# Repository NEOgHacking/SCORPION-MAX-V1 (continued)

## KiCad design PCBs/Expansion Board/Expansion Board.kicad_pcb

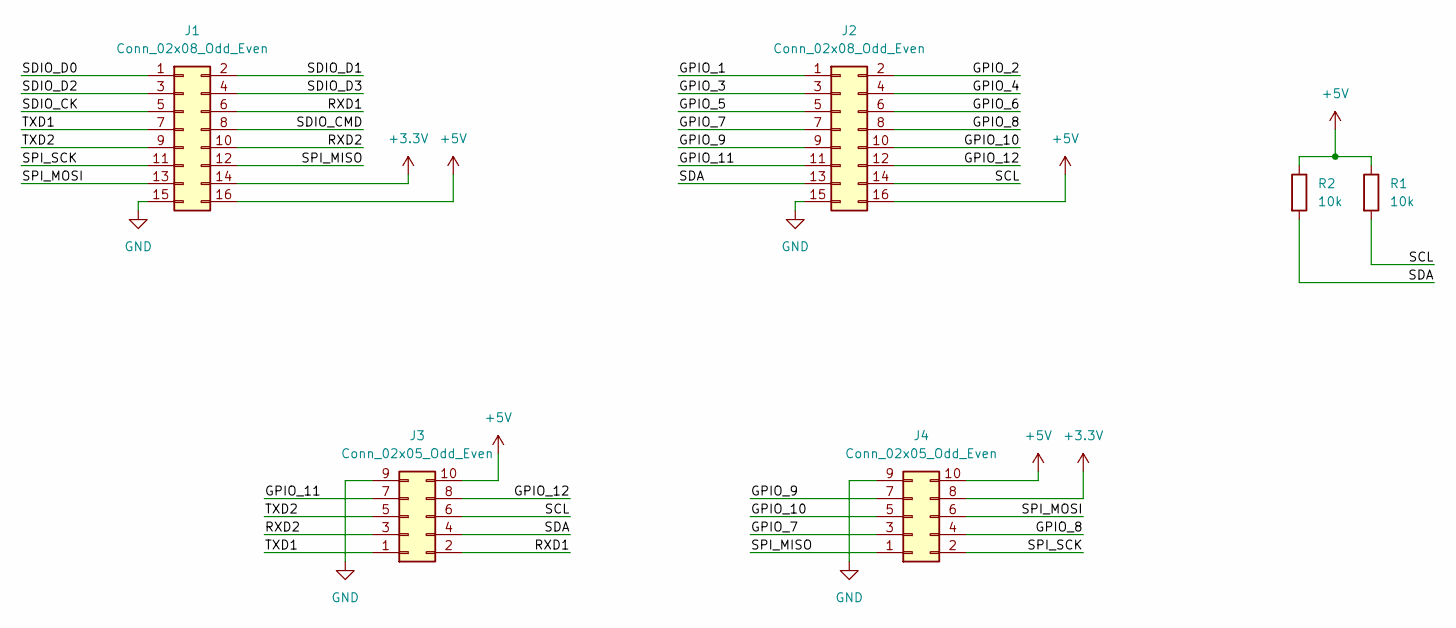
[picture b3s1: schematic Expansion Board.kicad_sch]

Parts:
J1, J2: Conn_02x08_Odd_Even; PinHeader_2x08_P2.54mm_Vertical
J3, J4: Conn_02x05_Odd_Even; IDC-Header_2x05_P2.54mm_Vertical
R1, R2: 10k; R_0603_1608Metric

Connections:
+3.3V: J1.14, J4.8
+5V: J1.16, J2.16, J3.10, J4.10, R1.1, R2.1
/GPIO_1: J2.1
/GPIO_2: J2.2
/GPIO_3: J2.3
/GPIO_4: J2.4
/GPIO_5: J2.5
/GPIO_6: J2.6
/GPIO_7: J2.7, J4.3
/GPIO_8: J2.8, J4.4
/GPIO_9: J2.9, J4.7
/GPIO_10: J2.10, J4.5
/GPIO_11: J2.11, J3.7
/GPIO_12: J2.12, J3.8
/RXD1: J1.6, J3.2
/RXD2: J1.10, J3.3
/SCL: J2.14, J3.6, R1.2
/SDA: J2.13, J3.4, R2.2
/SDIO_CK: J1.5
/SDIO_CMD: J1.8
/SDIO_D0: J1.1
/SDIO_D1: J1.2
/SDIO_D2: J1.3
/SDIO_D3: J1.4
/SPI_MISO: J1.12, J4.1
/SPI_MOSI: J1.13, J4.6
/SPI_SCK: J1.11, J4.2
/TXD1: J1.7, J3.1
/TXD2: J1.9, J3.5
GND: J1.15, J2.15, J3.9, J4.9

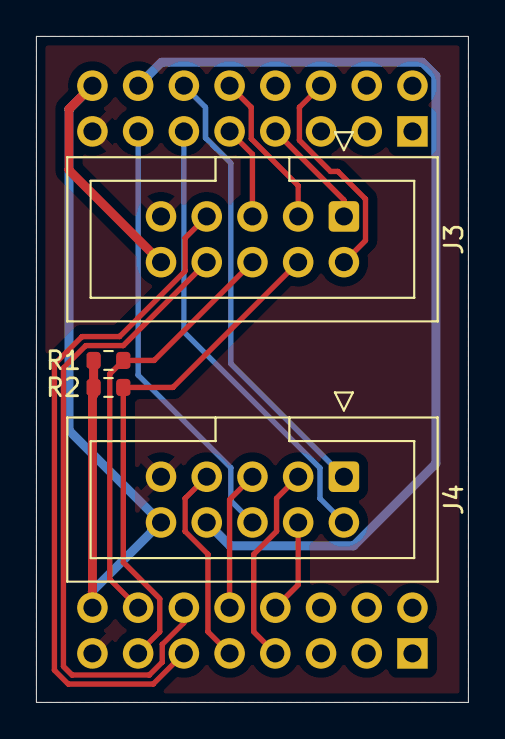
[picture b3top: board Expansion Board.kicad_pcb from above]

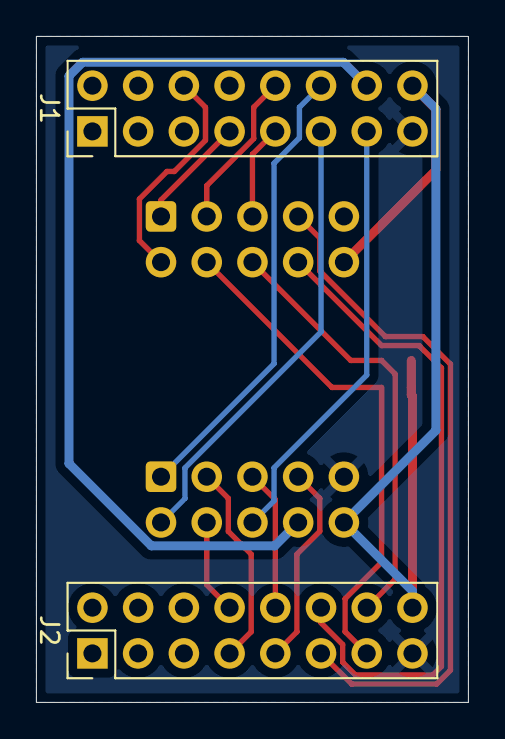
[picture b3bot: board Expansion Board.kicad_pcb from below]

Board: 2 copper layers, 24.0 x 37.0 mm, 6 parts (2 on the bottom side), 18 nets.

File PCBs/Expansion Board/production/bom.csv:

Designator,Footprint,Quantity,Value,LCSC Part #
"J1, J2",PinHeader_2x08_P2.54mm_Vertical,2,Conn_02x08_Odd_Even,
"J3, J4",IDC-Header_2x05_P2.54mm_Vertical,2,Conn_02x05_Odd_Even,
"R1, R2",0603,2,10k,

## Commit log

2026-01-10 git is so hard to use
2026-01-11 Updated KiCad files and made 3D files for expansion board and thermister board
2026-01-11 Updated all the files so its up to date
2026-01-11 Added Firmware for Marlin
2026-01-11 Modify header level in README.md
    Changed header from H1 to H3 for better hierarchy.
2026-01-11 Replace logo image in README
    Updated logo image in README.md to a new source URL.
2026-01-11 Update README with project details and images
    Added an image and expanded project description for clarity.
2026-01-11 Fix README formatting and enhance description
    Corrected formatting and improved readability of the README.
2026-01-11 Expand README with project reasoning and specs
    Added detailed specifications and reasoning for the mainboard design.
2026-01-11 Fix formatting and add newline in README.md
    Corrected formatting and added newline at end of file.
2026-01-11 Add USB port details to README
2026-01-11 Update README with schematic, PCB, and BOM information
    Added sections for schematic, PCB, and BOM details.
2026-01-11 Add images for PCB and related boards in README
2026-01-11 Add credits section to README
    Added credits section to acknowledge contributors.
2026-01-11 Added schematics in pdf format for the boards and interactive BOMs
2026-01-11 Updated render
2026-01-11 updated .blend
2026-01-11 Added pictures of prices in the BOM
2026-01-11 Fix typos and grammar in README.md
    Corrected typos and improved grammar in the README.
2026-01-11 Enhance README with firmware details and clarifications
    Added firmware information and updated component descriptions.
2026-01-11 Revise README for mainboard features and specifications
    Updated the README to improve clarity and detail about the main board's capabilities, including its specifications and intended use.
2026-01-11 Revise README section titles and add design overview
    Updated section titles and added a description of the board's design features.
2026-01-11 Enhance design description in README
    Expanded the design section to include details about PCB trace width and layout.
2026-01-11 Fix JLCPCB order price statement in README
    Corrected the pricing statement for the JLCPCB order.
2026-01-12 Made final changes before submiting
2026-01-12 Added start of video render
2026-01-14 Added .csv BOMs
    added .csv files
2026-01-14 Include schematic images in README
    Added images of schematics for various boards to README.
2026-03-26 Fixed some PCB stuff and rendering
2026-04-14 Added new clipper software cfg file
2026-04-14 Fixed .history track stuff
2026-04-15 Add video demonstration section to README
    Added a video link showcasing the functionality of the board.
2026-04-15 Added picture of the board
2026-04-15 Add images and update project description in README
